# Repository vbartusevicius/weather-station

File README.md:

# AeroMet V1 — Solid-State Roof Weather & Air-Quality Station

Open-source rooftop weather and air-quality station with **no moving parts** (`Ø 96 × 235 mm`, UV-stabilised ASA):
ultrasonic wind, acoustic rain and hail, UV / sunlight / night-sky brightness, temperature, humidity, pressure, lightning,
PM1 / PM2.5 / PM10, VOC / NOx and true CO₂. It runs from `12–32 V DC`, talks Wi-Fi and RS-485, serves its own web
dashboard and appears in Home Assistant by itself.

<table>
  <tr>
    <td width="34%"></td>
    <td width="66%"></td>
  </tr>
</table>

[What it measures](#what-it-measures) · [Hardware](#hardware) · [Web UI](#web-ui) · [Build one](#build-one) ·
[Firmware](#firmware) · [Development](#development)

## What it measures

| Measurement | Sensor | Range |
| :--- | :--- | :--- |
| Wind speed & direction | 4× 40 kHz ultrasonic transducers, time of flight (STM32G431 crown) | 0–60 m/s, 0.1° |
| Rain & hail | 4 piezo discs under the lid, acoustic impacts | 0–200 mm/h, hail size |
| UV index, UV-A / UV-B, sunlight, night sky | GUVB-C21SD + GUVA-C22SD photodiodes + TSL25911 under a PTFE dome | UVI 0–16+, 0.0002–88 000 lx |
| Temperature & humidity | Sensirion SHT40 in a 5-plate radiation shield | ±0.2 °C, ±1.8 % RH |
| Pressure & thunder | Bosch BMP585 | ±0.06 hPa |
| Particulates | Plantower PMSA003I | PM1 / PM2.5 / PM10 |
| VOC & NOx | Sensirion SGP41 + Gas Index Algorithm | index 1–500 |
| CO₂ | Sensirion SCD41 (heated below −8 °C) | 400–5000 ppm |
| Lightning | AS3935 + 500 kHz ferrite antenna | 1–40 km |
| Compass, tilt, vibration | MMC5983MA + LSM6DS3 | heading, mast tilt, ground vibration |

Full sensor, enclosure and board reference: **[docs/hardware.md](docs/hardware.md)**.

## Hardware

| Cutaway | Exploded | Every board on one breakaway panel |
| :---: | :---: | :---: |
|  |  |  |
| radiation shield, probe cartridge, base bay | 13 printed parts, bayonet and threaded joints | crown, main, probe, power, dome, reflector + legacy dome (4-layer, 120.1 × 76.1 mm) |

<details>
<summary><b>More renders</b>: inside view, every printed part, board plots</summary>

| Inside | Base | Pagoda | Wind tunnel |
| :---: | :---: | :---: | :---: |
|  |  |  |  |
| **Crown base** | **Crown lid** | **Struts** | **Probe sleeve** |
|  |  |  |  |

Board plots (top / bottom SVG): [crown](hardware/releases/v1/crown/renders/top.svg) ·
[main](hardware/releases/v1/main/renders/top.svg) · [probe](hardware/releases/v1/probe/renders/top.svg) ·
[power](hardware/releases/v1/power/renders/top.svg) · [dome](hardware/releases/v1/dome/renders/top.svg) ·
[reflector](hardware/releases/v1/reflector/renders/top.svg) · [panel](hardware/releases/v1/panel/renders/top.svg)

</details>

## Web UI

The station serves its dashboard over Wi-Fi (no cloud, no app). Every value is computed by the firmware; the page only
displays it.

| Now | Trends |
| :---: | :---: |
|  |  |
| live readings, forecast, sun & moon, air quality, lightning | any metrics from 1 hour to 6 months, wind rose, records, CSV export |
| **Calibration** | **Setup** |
|  |  |
| station health, home calibration with household items | Wi-Fi, MQTT / Home Assistant, RS-485 monitor, firmware update |

Also: MQTT with Home Assistant auto-discovery, and an RS-485 poll / response protocol (CRC-16 frames with every
sensor) for wired loggers.

## Build one

1. **Order the boards** with assembly: ODB++ for AISLER, Gerbers + MPN BOM + CPL for PCBWay / Eurocircuits, or the
   JLCPCB files for the breakaway panel ([`hardware/releases/v1/`](hardware/releases/v1/); which file goes where:
   [docs/building.md](docs/building.md#3-ordering-the-pcbs-and-assembly)).
2. **Print the enclosure**: 8 print plates in [`enclosure/print/`](hardware/releases/v1/enclosure/print/) (MJF / SLS
   nylon or ASA), plus standard O-rings and a turned PTFE dome.
3. **Assemble and seal**: harnesses, conformal coating and sealing in **[docs/building.md](docs/building.md)**.
4. **Flash** the station once over USB, then **bring it up and calibrate** it at home:
   **[CALIBRATION.md](CALIBRATION.md)**.

Open design questions and acceptance checks: [REVIEW_CHECKLIST.md](REVIEW_CHECKLIST.md).

## Firmware

Download from **[Releases](https://github.com/vbartusevicius/weather-station/releases)**: each release carries the
firmware, the complete hardware package (`aeromet-hardware.zip`: `boards/`, `enclosure/`, `optics/`, `docs/` and
self-assembly BOMs) and `SHA256SUMS.txt`. Every commit to `main` that passes CI is released, named after its UTC commit
time (`2026.10.24.0040`); the firmware reports the same version.

| File | Use |
| :--- | :--- |
| `usb-flash-firmware.bin` | first flash of a new board over USB: `esptool.py --chip esp32c6 write_flash 0x0 usb-flash-firmware.bin` |
| `firmware.bin` | later updates from the Web UI (Setup → Firmware update); carries the crown firmware too |
| `aeromet-hardware.zip` | complete manufacturing package (`boards/`, `enclosure/`, `optics/`, `docs/`, BOMs) |
| `SHA256SUMS.txt` | SHA-256 checksums for every release file above |

The version is the UTC commit time, `yyyy.mm.dd.hhmm`. Local build: `python3 station/scripts/release_firmware.py`
→ `station/build/firmware/`.

## Development

| Folder | Contents |
| :--- | :--- |
| [`hardware/`](hardware/) | spec (`product/spec.yaml`), SKiDL circuits, KiCad layouts, simulations, release package |
| [`mechanical/`](mechanical/) | CadQuery enclosure generator and renderer |
| [`station/`](station/) | ESP32-C6 firmware (ESP-IDF), Web UI (`station/data/`), simulator, unit and Web UI tests |
| [`crown/`](crown/) | STM32G431 crown firmware (ultrasonic wind, rain, lightning) |

```bash
python3 hardware/scripts/build.py                     # everything: hardware, CAD, release, firmware, tests
docker compose --profile lint run --rm -T cpp-lint "pio test -d station -e native"   # firmware unit tests
python3 station/scripts/mock_webui_server.py          # Web UI on the simulator: http://127.0.0.1:8765
docker compose --profile lint run --rm lint check .   # lint
python3 docs/render_readme_images.py                  # refresh the README screenshots and PCB render
```

Architecture, pipeline internals and every command: [docs/development.md](docs/development.md); agent instructions: [AGENTS.md](AGENTS.md).

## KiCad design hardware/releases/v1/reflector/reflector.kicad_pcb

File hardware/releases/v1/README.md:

# AeroMet V1 Hardware Release Package (6 Boards on 1 Breakaway Panel + 13-Part Enclosure)

Generated by `python3 hardware/scripts/build.py` (`release.py`) from `hardware/layout/v1/` and `mechanical/`: per-board
KiCad DRC reports (`<board>/drc.json`), ODB++ (AISLER; also PCBWay / Eurocircuits), Gerber X2 + drills + IPC-D-356
netlist, a generic MPN BOM and placement file (PCBWay, Eurocircuits), JLCPCB BOM / CPL, hand-fit lists,
STEP models and renders; every JLCPCB SMT part verified pin-for-pin against its EasyEDA footprint. Which file goes to
which fab house: [`docs/building.md`](../../../docs/building.md#3-ordering-the-pcbs-and-assembly). Design status and open prototype checks:
[`REVIEW_CHECKLIST.md`](../../../REVIEW_CHECKLIST.md); commissioning: [`CALIBRATION.md`](../../../CALIBRATION.md).

| Board | Size | Layers | Thickness | Role in the Station | Folder |
| :--- | :---: | :---: | :---: | :--- | :---: |
| **Breakaway Panel (`panel`)** | **`120.1 × 76.1 mm`** | **4** | **`1.6 mm`** | **All six boards + the legacy `dome_legacy` on one PCB (column packing, tabs clear of parts; order with "edge rails / fiducials added by JLCPCB"), double-sided assembly** | **`panel/`** |
| **1. `main`** | `32.0 × 52.0 mm` | 4 | `1.6 mm` | Right half of the base bay: 4-pole terminal `J1` (`12–32 V` + `RS-485 A/B`), `1.1 A` / `60 V` PTC, `SMAJ36A` TVS, `SS16` reverse-polarity diode, socketed `XIAO ESP32-C6` behind an `LM66100`, `SP3485EN` RS-485 (separate TX / RX / DE, `390 Ω` fail-safe bias, `PSM712` TVS, optional `120 Ω` `R26`), `LSM6DS3TR-C` IMU, `ADS1115` heater monitor, `AO3400A` reflector heater switch, crown control lines. Power nets `0.4 mm`. | `main/` |
| **2. `crown`** | `60 × 60 mm` (notched) | 4 | `1.6 mm` | `STM32G431RBT6` (I²C peripheral `0x2A`): 4× `UCC27524` H-bridge transducer drivers on `+12V_HEAT` with `BAV99` T/R isolation, `74HC4052` + `TLV9062` receive chain into the OPAMP1 PGA biased at VREF (PA3), piezo charge amplifier (22k / 1 nF anti-alias), `AS3935` + `MA5532-AE` on SPI1, `MMC5603NJ` compass, `XC6206` LDO, dome socket `J10`, spare `+12V_HEAT` `J11`, SWD footprint `J12`. | `crown/` |
| **3. `reflector`** | `24.0 × 24.0 mm` | 4 | `1.6 mm` | De-icing heater under the reflector cone: 4× `120 Ω` `2512` `2 W` in parallel on `+12V_HEAT` (`30 Ω`, `4.5 W` regulated), `10k` NTC `TH1`, 4-pin SMD male header `J1` to probe `J2`. | `reflector/` |
| **4. `dome`** | `Ø 15.6 mm` round | 4 | `1.6 mm` | UV / visible / NIR micro-PCB under the default flanged PTFE dome diffuser (lathe or CNC version; backup: the `Ø 20 × 2 mm` `JGS1` window in `crown_window`): `GUVB-C21SD` UV-B + `GUVA-C22SD` UV-A photodiodes, `TLV9062`, `ADS1115` (0x49), `TSL25911FN`, 4-pin B2B header `J1`. | `dome/` |
| `dome_legacy` | `Ø 13.6 mm` round | 4 | `1.6 mm` | Backup dome, same riser: `LTR-390UV-01` (discontinued), `TSL25911FN`, `GUVB-C31SM` (obsolete). Released separately (not on the panel, not in the order files). | `dome_legacy/` |
| **5. `probe`** | `14.0 × 56.0 mm` | 4 | `1.6 mm` | Vertical pagoda stem, bottom to top: `J1`, slot, `SHT40-AD1F-R2`, slot (no ground plane in its bridges), `SGP41-D-R4` + `BMP585`, `SCD41-D-R2` with the backside `0.42 W` heater and `LM2903` `−7.6 °C` thermostat, right-angle socket `J2` to the reflector. | `probe/` |
| **6. `power`** | `28.5 × 21.5 mm` | 4 | `1.6 mm` | Flat under `main`: 2× `TPS54360` (`743 kHz`) → `+5V` electronics and `+12V_HEAT` (heaters, transducer drive), `AP2112K-3.3` → `+3V3_PROBE`, 10-pin JST-SH `J1` to main `J5`. | `power/` |

Enclosure (`enclosure/`): assembled-position STL / STEP per part, `print/<plate>.stl` (8 print plates, the only files to
print), renders, and purchase drawings in `drawings/`: `ptfe_dome_lathe.svg` / `ptfe_dome_cnc.svg` (default UV / light cover:
flanged PTFE dome, lathe version from round rod or CNC hemisphere version; matching `ptfe_dome_<kind>.step` in the lathe frame for
the CNC quote) and `jgs1_window.svg` (backup window, `crown_window`
top).

Hand assembly: every board folder has `<board>_assembly.pdf`: one page per populated side (bottom mirrored, as seen
from below), every part with reference + value, a red dot on pin 1 (ICs, connectors, diodes), `[H]` on hand-fitted
parts, same value = same colour, large parts dashed (fit them last), and a value list with quantities and references.

Print process: the enclosure is designed for MJF / SLS PA12 (powder nylon, ~±0.3 mm), but **no part of it has been
printed yet** (no tested process). Design rules it follows (`mechanical/tests/test_print_rules.py`): snap beams ≤ 2.5 %
strain, hook undersides ≥ 0.3 mm above the board with a lead-in ramp, printed threads 0.30 mm flank clearance per side,
separate bodies on one plate ≥ 0.3 mm apart (reset button 0.40 mm), engraved marks ≥ 0.6 mm deep and ≥ 3 mm. Check on the
first print: clip snap force, thread fit (strut M12 + locknuts, probe sleeve M22, dome / window nuts M22), the three
bayonet joints locking, the reset button and umbrella moving freely, and the lock marks being readable.

## Parts orders for self-assembly (one complete station)

Generated by `hardware/scripts/order_parts.py` with every release (`release.py`); `hardware/tests/test_order_files.py`
fails when they differ from a fresh export. Live stock check: `python3 hardware/scripts/order_parts.py --check`.

| File | Upload to | Column mapping |
| :--- | :--- | :--- |
| `order_lcsc.csv` | lcsc.com → **BOM Tool** → Upload BOM | `LCSC Part Number` → *LCSC Part #*, `Quantity` → *Quantity*; optional `Manufacturer Part Number` → *MPN*, `Designators` → *Designator*, `Value` / `Footprint` → *Comment* / *Footprint*. Set the multiplier to 1 (one station); LCSC rounds each line up to its minimum order. |
| `order_elsewhere.csv` | by hand, per shop | electronics the LCSC store does not sell: `Mouser` / `Digi-Key` / `TME` columns (several numbers per shop separated by ` / `, the first preferred) + `Other sources`. General hardware (fasteners, O-rings, cable gland, thermal filler, coating, UV cover) and printed parts are only in `assembly_parts.csv` (column `Category`) |

`order_lcsc.csv` merges all boards (the legacy dome as `dome_legacy:ref`) into one line per LCSC number (designators `board:ref`) and adds the off-board
parts whose `Part` names an LCSC number. JLCPCB numbers the LCSC store does not stock are swapped for verified store
numbers in `hardware/product/lcsc_store.yaml` (the board BOMs keep the JLCPCB numbers). Parts the LCSC store does not sell (Sensirion SCD41 / SGP41 / SHT40, AS3935) are listed in
`order_elsewhere.csv` with a verified distributor (TME / Farnell / RS) from the `elsewhere:` section of that file. Run `--check` before ordering:
store stock changes daily, and the check lists every line that cannot be ordered as it stands.

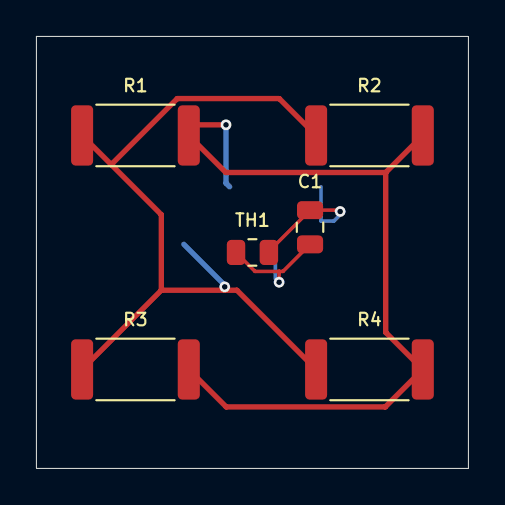
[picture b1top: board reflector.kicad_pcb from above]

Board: 4 copper layers, 24.0 x 24.0 mm, 7 parts (1 on the bottom side), 4 nets.

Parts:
C1: 100n 50V; C_0805_2012Metric
J1: Probe T-Header SMD; HX_PZ2.54-1x4P-SMD
R1, R2, R3, R4: 120R; R_2512_6332Metric
TH1: 10k NTC; R_0805_2012Metric

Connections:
+12V_HEAT: J1.1, R1.1, R2.1, R3.1, R4.1
GND: C1.2, J1.4, TH1.2
HEAT_SW: J1.2, R1.2, R2.2, R3.2, R4.2
NTC_SENSE: C1.1, J1.3, TH1.1

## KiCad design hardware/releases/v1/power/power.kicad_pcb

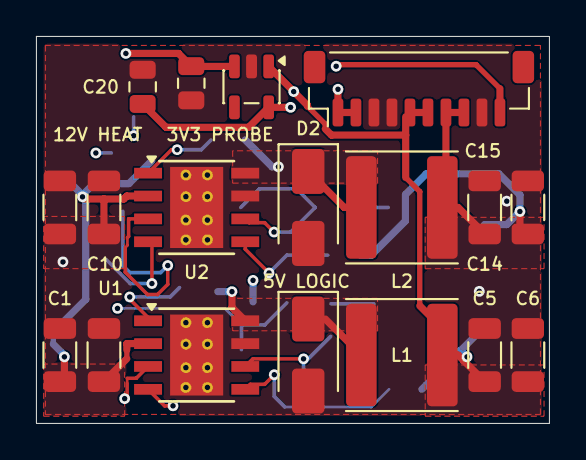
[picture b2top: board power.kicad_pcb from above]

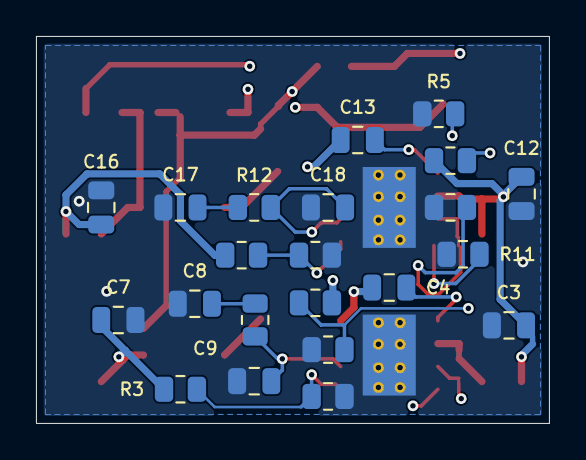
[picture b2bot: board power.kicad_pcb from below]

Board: 4 copper layers, 28.5 x 21.5 mm, 40 parts (22 on the bottom side), 19 nets.

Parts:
C1, C2, C10, C11: 2u2 100V; C_1206_3216Metric
C3, C12: 100n 100V; C_0805_2012Metric
C4, C7, C13, C16: 100n 50V; C_0805_2012Metric
C5, C6: 47u 10V; C_1206_3216Metric
C8: 33n 50V; C_0805_2012Metric
C9, C18: 68p C0G 50V; C_0805_2012Metric
C14, C15: 22u 25V; C_1206_3216Metric
C17: 18n 50V; C_0805_2012Metric
C19: 1u 50V; C_0805_2012Metric
C20: 10u 10V; C_0805_2012Metric
D1, D2: B360A; D_SMA
J1: Main board; JST_SH_BM10B-SRSS-TB_1x10-1MP_P1.00mm_Vertical
L1: 8.2uH; L_Sunlord_SWPA6045S
L2: 22uH; L_Sunlord_SWPA6045S
R1, R7: 511k; R_0805_2012Metric
R2, R8: 82k5; R_0805_2012Metric
R3: 53k6; R_0805_2012Metric
R4: 10k2; R_0805_2012Metric
R5, R11: 130k; R_0805_2012Metric
R6, R12: 6k49; R_0805_2012Metric
R9: 140k; R_0805_2012Metric
R10: 10k; R_0805_2012Metric
U1, U2: TPS54360DDAR; TI_SO-PowerPAD-8_ThermalVias
U3: AP2112K-3.3; SOT-23-5

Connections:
+3V3_PROBE: C20.1, J1.10, U3.5
+5V: C5.1, C6.1, C7.1, C19.1, J1.5, J1.6, L1.2, R3.1, U3.1, U3.3
+12V_HEAT: C14.1, C15.1, C16.1, J1.7, J1.8, L2.2, R9.1
GND: C1.2, C2.2, C3.2, C5.2, C6.2, C7.2, C8.2, C9.2, C10.2, C11.2, C12.2, C14.2, C15.2, C16.2, C17.2, C18.2, C19.2, C20.2, D1.2, D2.2, J1.3, J1.4, J1.9, R2.2, R4.2, R5.2, R8.2, R10.2, R11.2, U1.7, U1.9, U2.7, U2.9, U3.2
HEAT_BST: C13.1, U2.1
HEAT_CC: C17.1, R12.2
HEAT_COMP: C18.1, R12.1, U2.6
HEAT_EN: R7.2, R8.1, U2.3
HEAT_FB: R9.2, R10.1, U2.5
HEAT_RT: R11.1, U2.4
HEAT_SW: C13.2, D2.1, L2.1, U2.8
LOGIC_BST: C4.1, U1.1
LOGIC_CC: C8.1, R6.2
LOGIC_COMP: C9.1, R6.1, U1.6
LOGIC_EN: R1.2, R2.1, U1.3
LOGIC_FB: R3.2, R4.1, U1.5
LOGIC_RT: R5.1, U1.4
LOGIC_SW: C4.2, D1.1, L1.1, U1.8
VIN_PROT: C1.1, C2.1, C3.1, C10.1, C11.1, C12.1, J1.1, J1.2, R1.1, R7.1, U1.2, U2.2

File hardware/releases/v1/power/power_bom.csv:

Line,Qty,Designators,Value,Package,Type,Manufacturer,MPN,LCSC,Assembly
1,4,"C1,C10,C11,C2",2u2 100V,C_1206_3216Metric,SMD,Samsung,CL31B225KCHSNNE,C170101,machine
2,2,"C12,C3",100n 100V,C_0805_2012Metric,SMD,YAGEO,CC0805KKX7R0BB104,C106243,machine
3,4,"C13,C16,C4,C7",100n 50V,C_0805_2012Metric,SMD,YAGEO,CC0805KRX7R9BB104,C49678,machine
4,2,"C14,C15",22u 25V,C_1206_3216Metric,SMD,Samsung,CL31A226KAHNNNE,C12891,machine
5,1,C17,18n 50V,C_0805_2012Metric,SMD,YAGEO,CC0805JRX7R9BB183,C520032,machine
6,2,"C18,C9",68p C0G 50V,C_0805_2012Metric,SMD,YAGEO,CC0805JRNPO9BN680,C107120,machine
7,1,C19,1u 50V,C_0805_2012Metric,SMD,Samsung,CL21B105KBFNNNE,C28323,machine
8,1,C20,10u 10V,C_0805_2012Metric,SMD,Samsung,CL21A106KPFNNNE,C17024,machine
9,2,"C5,C6",47u 10V,C_1206_3216Metric,SMD,Samsung,CL31A476MPHNNNE,C96123,machine
10,1,C8,33n 50V,C_0805_2012Metric,SMD,YAGEO,CC0805KRX7R9BB333,C107150,machine
11,2,"D1,D2",B360A,D_SMA,SMD,Diodes Inc,B360A-13-F,C94193,machine
12,1,J1,Main board,JST_SH_BM10B-SRSS-TB_1x10-1MP_P1.00mm_Vertical,SMD,JST,BM10B-SRSS-TB(LF)(SN),C160396,machine
13,1,L1,8.2uH,L_Sunlord_SWPA6045S,SMD,APV,ANR6045T8R2M,C7427168,machine
14,1,L2,22uH,L_Sunlord_SWPA6045S,SMD,Bourns,SRN6045TA-220M,C2044314,machine
15,2,"R1,R7",511k,R_0805_2012Metric,SMD,UNI-ROYAL,0805W8F5113T5E,C17735,machine
16,1,R10,10k,R_0805_2012Metric,SMD,UNI-ROYAL,0805W8F1002T5E,C17414,machine
17,2,"R11,R5",130k,R_0805_2012Metric,SMD,UNI-ROYAL,0805W8F1303T5E,C17450,machine
18,2,"R12,R6",6k49,R_0805_2012Metric,SMD,UNI-ROYAL,0805W8F6491T5E,C17769,machine
19,2,"R2,R8",82k5,R_0805_2012Metric,SMD,YAGEO,RC0805FR-0782K5L,C276314,machine
20,1,R3,53k6,R_0805_2012Metric,SMD,UNI-ROYAL,0805W8F5362T5E,C21398,machine
21,1,R4,10k2,R_0805_2012Metric,SMD,UNI-ROYAL,0805W8F1022T5E,C17402,machine
22,1,R9,140k,R_0805_2012Metric,SMD,UNI-ROYAL,0805W8F1403T5E,C17460,machine
23,2,"U1,U2",TPS54360DDAR,TI_SO-PowerPAD-8_ThermalVias,SMD,Texas Instruments,TPS54360DDAR,C44377,machine
24,1,U3,AP2112K-3.3,SOT-23-5,SMD,Diodes Inc.,AP2112K-3.3TRG1,C51118,machine

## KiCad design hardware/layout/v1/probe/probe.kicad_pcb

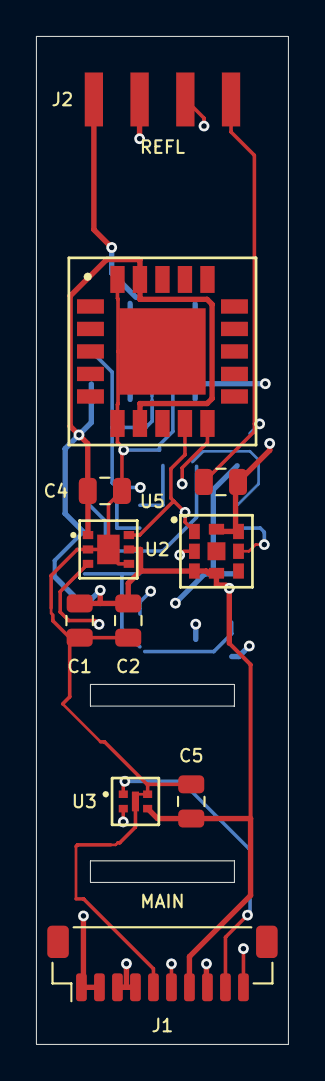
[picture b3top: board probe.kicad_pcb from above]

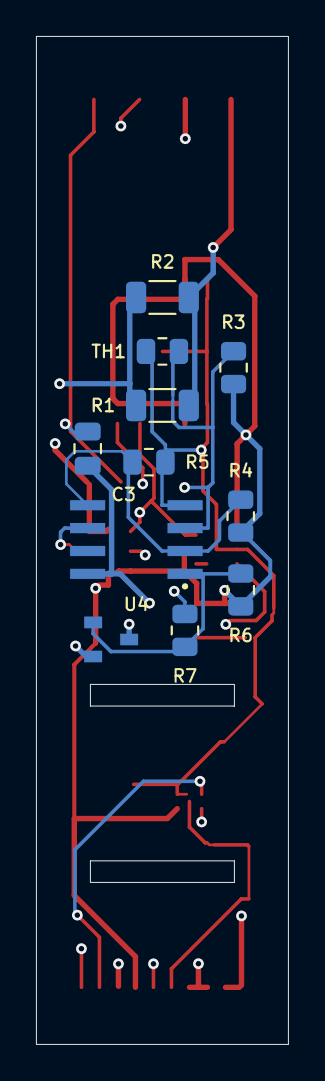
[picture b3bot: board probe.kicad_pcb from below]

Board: 4 copper layers, 14.0 x 56.0 mm, 22 parts (11 on the bottom side), 12 nets.

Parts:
C1: 10u 10V; C_0805_2012Metric
C2, C3, C4, C5, C6: 100n 50V; C_0805_2012Metric
J1: Main board; JST_SH_BM10B-SRSS-TB_1x10-1MP_P1.00mm_Vertical
J2: Reflector T-Socket SMD; HX_PM2.54-1x4P-RA-SMD
Q1: AO3400A; AOS_AO3400A_SOT-23
R1, R2: 680R; R_1206_3216Metric
R3, R4, R6: 10k; R_0805_2012Metric
R5: 47k; R_0805_2012Metric
R7: 470k; R_0805_2012Metric
TH1: 10k NTC; R_0805_2012Metric
U1: SCD41-D-R2; Sensirion_SCD41_LGA-20
U2: SGP41-D-R4; Sensirion_SGP41_DFN-6
U3: SHT40-AD1F-R2; Sensirion_SHT45_DFN-4
U4: LM2903DR2G; ON_LM393DR2G_SOIC-8
U5: BMP585; Bosch_BMP585_LGA-9

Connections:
+3V3_PROBE: C1.1, C2.1, C4.1, C5.1, C6.1, J1.7, R3.1, R4.1, R6.1, U1.7, U1.19, U2.1, U2.5, U3.3, U5.3, U5.4, U5.7, U5.8
+12V_HEAT: C3.1, J1.1, J1.2, J2.1, R1.1, R2.1, U4.8
CO2_GATE: Q1.1, R6.2, R7.1, U4.1
CO2_HEAT_RTN: J1.8, Q1.2
CO2_HEAT_SW: Q1.3, R1.2, R2.2
CO2_NTC: R3.2, R7.2, TH1.1, U4.3
CO2_VSET: R4.2, R5.1, U4.2, U4.5
GND: C1.2, C2.2, C3.2, C4.2, C5.2, C6.2, J1.5, J2.4, R5.2, TH1.2, U1.6, U1.20, U1.21, U2.2, U2.4, U2.7, U3.4, U3.5, U4.4, U4.6, U5.6
HEAT_SW: J1.3, J1.4, J2.2
I2C_SCL: J1.10, U1.9, U2.6, U3.2, U5.1
I2C_SDA: J1.9, U1.10, U2.3, U3.1, U5.2
NTC_SENSE: J1.6, J2.3

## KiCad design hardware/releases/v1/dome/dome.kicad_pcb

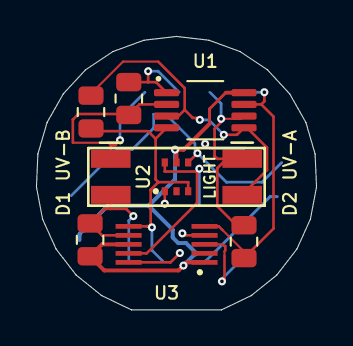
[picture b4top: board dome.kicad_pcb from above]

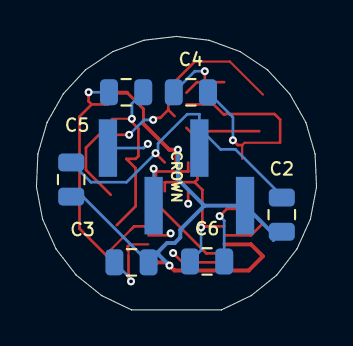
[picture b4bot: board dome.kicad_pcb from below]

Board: 4 copper layers, 15.6 x 15.2 mm, 16 parts (7 on the bottom side), 9 nets.

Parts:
C1, C2, C3: 100n 50V; C_0805_2012Metric
C4: 10n 50V; C_0805_2012Metric
C5: 22n 50V; C_0805_2012Metric
C6: 1u 50V; C_0805_2012Metric
D1: GUVB-C21SD; Genicom_COB2418
D2: GUVA-C22SD; Genicom_COB2418
J1: CROWN_RISER; HX_PZ2.54-1x4P-SMD
R1: 10M; R_0805_2012Metric
R2: 4M7; R_0805_2012Metric
R3: 100k; R_0805_2012Metric
R4: 10k; R_0805_2012Metric
U1: TLV9062IDGKR; TI_TLV9062_VSSOP-8
U2: TSL25911FN; AMS_TSL25911FN
U3: ADS1115IDGSR; TI_ADS1115_VSSOP-10

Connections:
+3V3: C1.1, C2.1, C3.1, J1.1, R3.1, U1.8, U2.5, U3.1, U3.8
GND: C1.2, C2.2, C3.2, C6.2, J1.2, R4.2, U1.4, U2.3, U2.4, U3.3, U3.6
I2C_SCL: J1.4, U2.1, U3.10
I2C_SDA: J1.3, U2.6, U3.9
UVA_IN: C5.1, D2.2, R2.1, U1.6
UVA_OUT: C5.2, R2.2, U1.7, U3.5
UVB_IN: C4.1, D1.2, R1.1, U1.2
UVB_OUT: C4.2, R1.2, U1.1, U3.4
UV_VB: C6.1, D1.1, D2.1, R3.2, R4.1, U1.3, U1.5, U3.7

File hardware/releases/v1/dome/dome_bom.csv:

Line,Qty,Designators,Value,Package,Type,Manufacturer,MPN,LCSC,Assembly
1,3,"C1,C2,C3",100n 50V,C_0805_2012Metric,SMD,YAGEO,CC0805KRX7R9BB104,C49678,machine
2,1,C4,10n 50V,C_0805_2012Metric,SMD,YAGEO,CC0805KRX7R9BB103,C83170,machine
3,1,C5,22n 50V,C_0805_2012Metric,SMD,YAGEO,CC0805KRX7R9BB223,C107147,machine
4,1,C6,1u 50V,C_0805_2012Metric,SMD,Samsung,CL21B105KBFNNNE,C28323,machine
5,1,D1,GUVB-C21SD,Genicom_COB2418,SMD,Genicom,GUVB-C21SD,,hand-fit (not stocked by JLCPCB)
6,1,D2,GUVA-C22SD,Genicom_COB2418,SMD,Genicom,GUVA-C22SD,,hand-fit (not stocked by JLCPCB)
7,1,J1,CROWN_RISER,HX_PZ2.54-1x4P-SMD,SMD,HCTL,HX PZ2.54-1x4P TP-YQ,C41417361,machine
8,1,R1,10M,R_0805_2012Metric,SMD,UNI-ROYAL,0805W8F1005T5E,C26108,machine
9,1,R2,4M7,R_0805_2012Metric,SMD,UNI-ROYAL,0805W8F4704T5E,C17674,machine
10,1,R3,100k,R_0805_2012Metric,SMD,UNI-ROYAL,0805W8F1003T5E,C149504,machine
11,1,R4,10k,R_0805_2012Metric,SMD,UNI-ROYAL,0805W8F1002T5E,C17414,machine
12,1,U1,TLV9062IDGKR,TI_TLV9062_VSSOP-8,SMD,Texas Instruments,TLV9062IDGKR,C398356,machine
13,1,U2,TSL25911FN,AMS_TSL25911FN,SMD,ams OSRAM,TSL25911FN,C176812,machine
14,1,U3,ADS1115IDGSR,TI_ADS1115_VSSOP-10,SMD,Texas Instruments,ADS1115IDGSR,C37593,machine

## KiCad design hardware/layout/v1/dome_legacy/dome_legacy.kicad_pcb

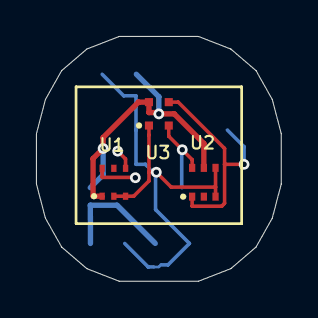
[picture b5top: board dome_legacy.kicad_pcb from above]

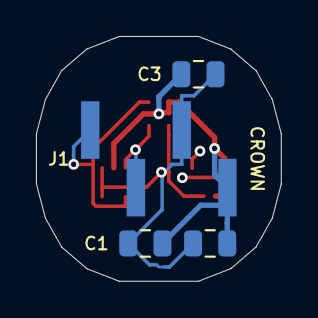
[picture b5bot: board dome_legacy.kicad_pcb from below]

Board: 4 copper layers, 13.6 x 13.6 mm, 7 parts (4 on the bottom side), 4 nets.

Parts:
C1, C2: 100n 50V; C_0805_2012Metric
C3: 1u 50V; C_0805_2012Metric
J1: CROWN_RISER; HX_PZ2.54-1x4P-SMD
U1: LTR-390UV-01; LiteOn_LTR-390UV-01
U2: TSL25911FN; AMS_TSL25911FN
U3: GUVB-C31SM; GenUV_GUVB-C31SM

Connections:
+3V3: C1.1, C2.1, C3.1, J1.1, U1.1, U2.5, U3.4
GND: C1.2, C2.2, C3.2, J1.2, U1.2, U1.3, U2.3, U2.4, U3.1
I2C_SCL: J1.4, U1.4, U2.1, U3.3
I2C_SDA: J1.3, U1.6, U2.6, U3.2

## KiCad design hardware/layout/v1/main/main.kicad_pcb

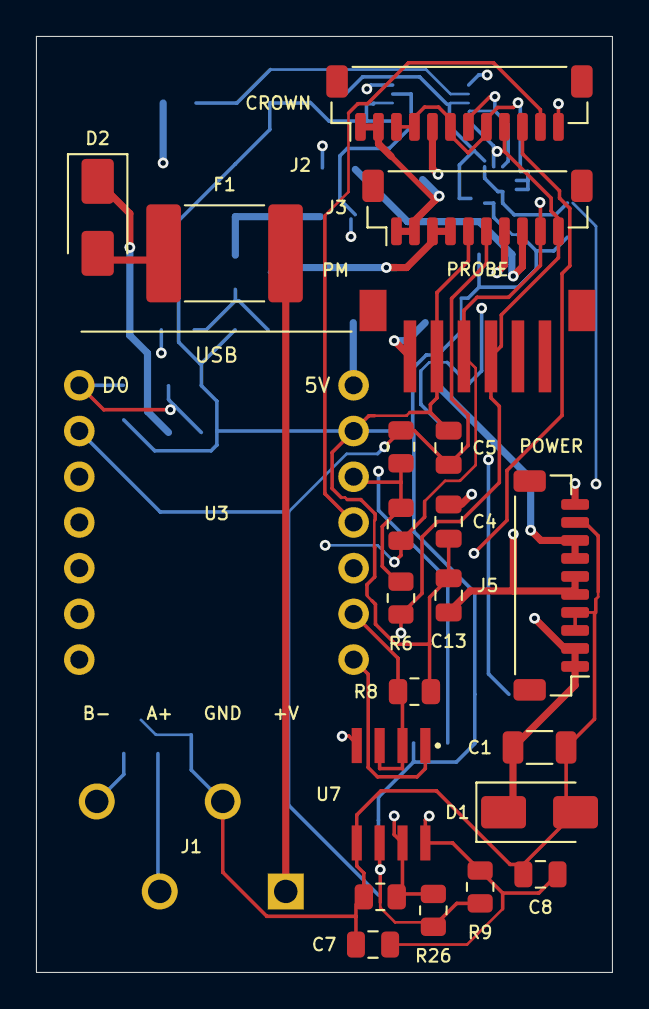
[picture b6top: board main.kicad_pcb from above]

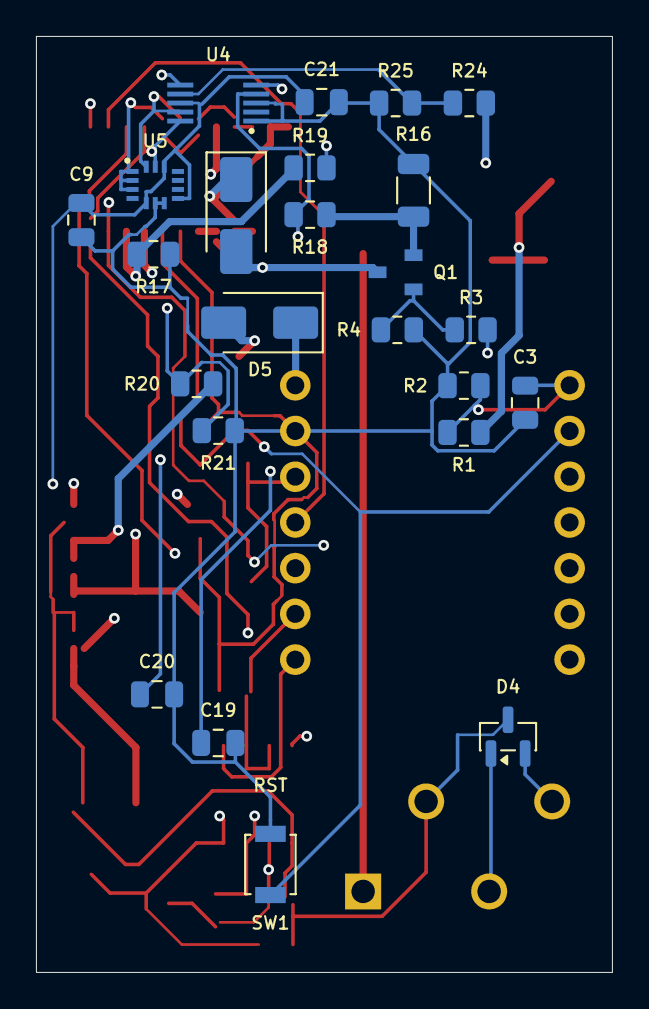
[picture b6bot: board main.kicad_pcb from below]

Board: 4 copper layers, 32.0 x 52.0 mm, 47 parts (24 on the bottom side), 30 nets.

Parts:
C1: 2u2 100V; C_1206_3216Metric
C3, C5, C7, C8, C9, C21: 100n 50V; C_0805_2012Metric
C4, C13: 10u 10V; C_0805_2012Metric
C19, C20: 1u 50V; C_0805_2012Metric
D1: SMAJ36A; D_SMA
D2, D3: SS16; D_SMA
D4: PSM712; SOT-23
D5: SS14; D_SMA
F1: 1.1A; Fuse_2920_7451Metric
J1: 12-32V + RS485; TerminalBlock_Kefa_KF250-3.5-4P
J2: Crown board; JST_SH_BM12B-SRSS-TB_1x12-1MP_P1.00mm_Vertical
J3: Probe board; JST_SH_BM10B-SRSS-TB_1x10-1MP_P1.00mm_Vertical
J4: PMSA003I PM; JST_B6B-ZR-SM4-TF
J5: Power board; JST_SH_BM10B-SRSS-TB_1x10-1MP_P1.00mm_Vertical
Q1: AO3400A; AOS_AO3400A_SOT-23
R1, R4: 100k; R_0805_2012Metric
R2, R7, R8, R21, R24, R25: 10k; R_0805_2012Metric
R3: 330R; R_0805_2012Metric
R5, R6: 2k2; R_0805_2012Metric
R9, R10: 390R; R_0805_2012Metric
R16: 0R1; R_1206_3216Metric
R17: 1R; R_0805_2012Metric
R18, R19: 1k; R_0805_2012Metric
R20: 30k; R_0805_2012Metric
R26: 120R; R_0805_2012Metric
SW1: SERVICE; SW_SPST_B3U-1000P
U3: XIAO ESP32C6; XIAO_ESP32C6_Header
U4: ADS1115IDGSR; TI_ADS1115_VSSOP-10
U5: LSM6DS3TR-C; ST_LSM6DS3TR-C_LGA-14
U7: SP3485EN-L/TR; ON_LM393DR2G_SOIC-8

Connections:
+3V3: C7.1, C8.1, C9.1, C21.1, R5.1, R6.1, R7.1, R9.1, U3.12, U4.8, U5.5, U5.8, U5.12, U7.8
+3V3_PROBE: J3.7, J5.10
+5V: C13.1, D5.2, J2.5, J4.1, J5.5, J5.6, R24.1
+5V_XIAO: C4.1, D5.1, U3.14
+12V_HEAT: D3.1, J2.1, J2.2, J3.1, J3.2, J5.7, J5.8, R20.1
CO2_HEAT_RTN: J3.8, R17.1, R19.1
CROWN_BOOT0: J2.12, U3.3
CROWN_IRQ: J2.10, U3.10
CROWN_NRST: J2.11, U3.11
GND: C1.2, C3.2, C4.2, C5.2, C7.2, C8.2, C9.2, C13.2, C19.2, C20.2, C21.2, D1.2, D4.3, J1.2, J2.3, J2.4, J2.6, J2.8, J3.5, J4.2, J5.3, J5.4, J5.9, R2.2, R4.2, R8.2, R10.2, R16.2, R17.2, R21.2, R25.2, SW1.2, U3.13, U4.1, U4.3, U5.1, U5.2, U5.3, U5.6, U5.7, U7.5
HEAT_GATE: Q1.1, R3.2, R4.1
HEAT_PWM: R3.1, U3.4
HEAT_SENSE: Q1.2, R16.1, R18.1
HEAT_SW: D3.2, J3.3, J3.4, Q1.3
I2C_SCL: J2.9, J3.10, J4.4, R6.2, U3.6, U4.10, U5.13
I2C_SDA: J2.7, J3.9, J4.3, R5.2, U3.5, U4.9, U5.14
MON_5V: R20.2, R21.1, U4.6
MON_5V_LOGIC: R24.2, R25.1, U4.7
MON_PROBE: C20.1, R19.2, U4.5
MON_REFL: C19.1, R18.2, U4.4
NTC_SENSE: C5.1, J3.6, R7.2, SW1.1, U3.2
RS485_A: D4.1, J1.3, R9.2, R26.1, U7.6
RS485_B: D4.2, J1.4, R10.1, R26.2, U7.7
RS485_DE: R8.1, U3.9, U7.2, U7.3
RS485_RX: U3.8, U7.1
RS485_TX: U3.7, U7.4
VIN_ADC: C3.1, R1.2, R2.1, U3.1
VIN_FUSED: D2.2, F1.2
VIN_PROT: C1.1, D1.1, D2.1, J5.1, J5.2, R1.1
VIN_RAW: F1.1, J1.1
